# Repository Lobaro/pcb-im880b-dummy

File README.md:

# pcb-im880b-dummy
Skeleton KiCad Project for iM880b LoRa Module from www.imst.com

* Minimal Schematic 
* Module Footprint

Download KiCad here: 
http://kicad-pcb.org/download/

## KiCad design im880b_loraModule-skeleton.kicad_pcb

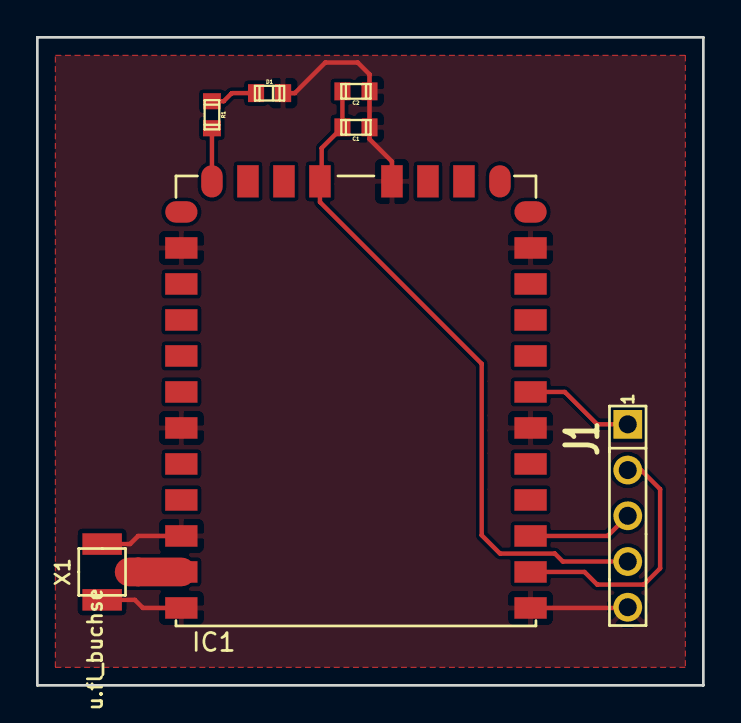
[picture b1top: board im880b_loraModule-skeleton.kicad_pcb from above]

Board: 2 copper layers, 37.0 x 36.0 mm, 7 parts (0 on the bottom side), 8 nets.

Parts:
C1: 100nF; 0603
C2: 1uF; 0603
D1: LED; 0603_D
IC1: iM880B
J1: CONN_01X05; HDR1x5
R1: 1K; 0603
X1: u.fl_buchse; ufl_smd

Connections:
/SWCLK: IC1.2, J1.2
/SWDIO: IC1.3, J1.3
/~Reset: IC1.7, J1.1
GND: C1.2, C2.2, D1.1, IC1.1, IC1.6, IC1.11, IC1.16, IC1.22, IC1.27, IC1.30, IC1.32, J1.5, X1.2
unnamed: D1.2, R1.2
unnamed: IC1.20, R1.1
unnamed: IC1.31, X1.1
VDD: C1.1, C2.1, IC1.17, J1.4

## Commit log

2017-05-02 initial import
